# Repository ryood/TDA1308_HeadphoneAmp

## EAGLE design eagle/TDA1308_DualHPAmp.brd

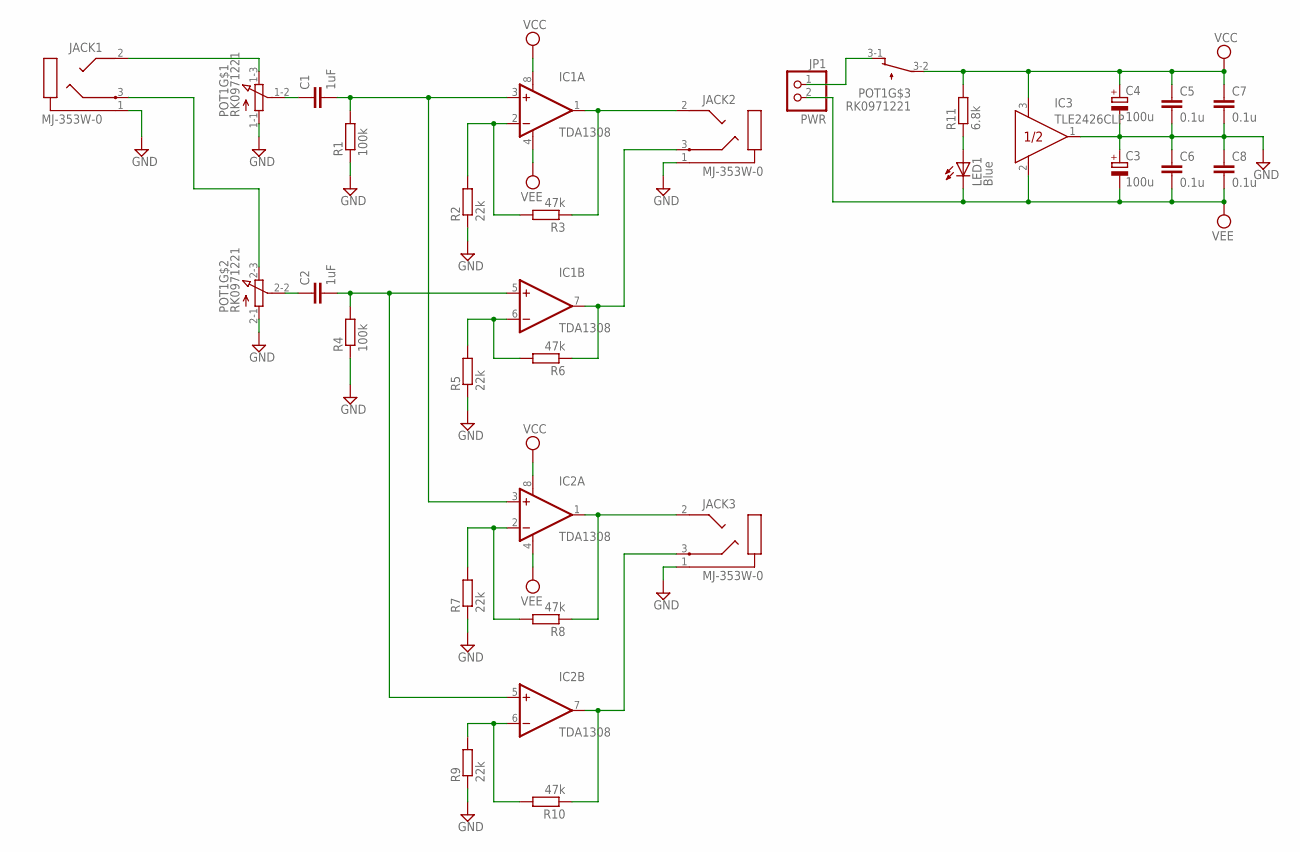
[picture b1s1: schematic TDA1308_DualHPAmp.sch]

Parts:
C1, C2: 1uF; C050-050X075
C3, C4: 100u; E2,5-7
C5, C7: 0.1u; C050-024X044
C6, C8: 0.1u; C025-024X044
IC1, IC2: TDA1308; DIL08
IC3: TLE2426CLP; TO226AA
JACK1, JACK2, JACK3: MJ-353W-0; MJ-3052W-0
JP1: PWR; 1X02
LED1: Blue; LED3MM
POT1: RK0971221
R1, R4: 100k; 0207/2V
R2, R7, R9: 22k; 0207/2V
R3, R6, R8, R10: 47k; 0207/2V
R5: 22k; 0207/7
R11: 6.8k; 0207/7

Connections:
GND: C3.+, C4.-, C5.2, C6.1, C7.2, C8.1, IC3.1 (OUT), JACK1.1, JACK2.1, JACK3.1, POT1.1-1 (A), POT1.2-1 (A), R1.1, R2.1, R4.1, R5.1, R7.1, R9.1
unnamed: JACK1.2, POT1.1-3 (E)
unnamed: JACK1.3, POT1.2-3 (E)
unnamed: C1.1, POT1.1-2 (S)
unnamed: C2.1, POT1.2-2 (S)
unnamed: C2.2, IC1.5 (+IN), IC2.5 (+IN), R4.2
unnamed: C1.2, IC1.3 (+IN), IC2.3 (+IN), R1.2
unnamed: IC1.2 (-IN), R2.2, R3.2
unnamed: IC1.1 (OUT), JACK2.2, R3.1
unnamed: IC1.6 (-IN), R5.2, R6.2
unnamed: JP1.1, POT1.3-1 (O)
unnamed: IC1.7 (OUT), JACK2.3, R6.1
unnamed: IC2.2 (-IN), R7.2, R8.2
unnamed: LED1.A, R11.1
unnamed: IC2.6 (-IN), R9.2, R10.2
unnamed: IC2.1 (OUT), JACK3.2, R8.1
unnamed: IC2.7 (OUT), JACK3.3, R10.1
VCC: C4.+, C5.1, C7.1, IC1.8 (V+), IC2.8 (V+), IC3.3 (IN), POT1.3-2, R11.2
VEE: C3.-, C6.2, C8.2, IC1.4 (V-), IC2.4 (V-), IC3.2 (COM), JP1.2, LED1.K (C)

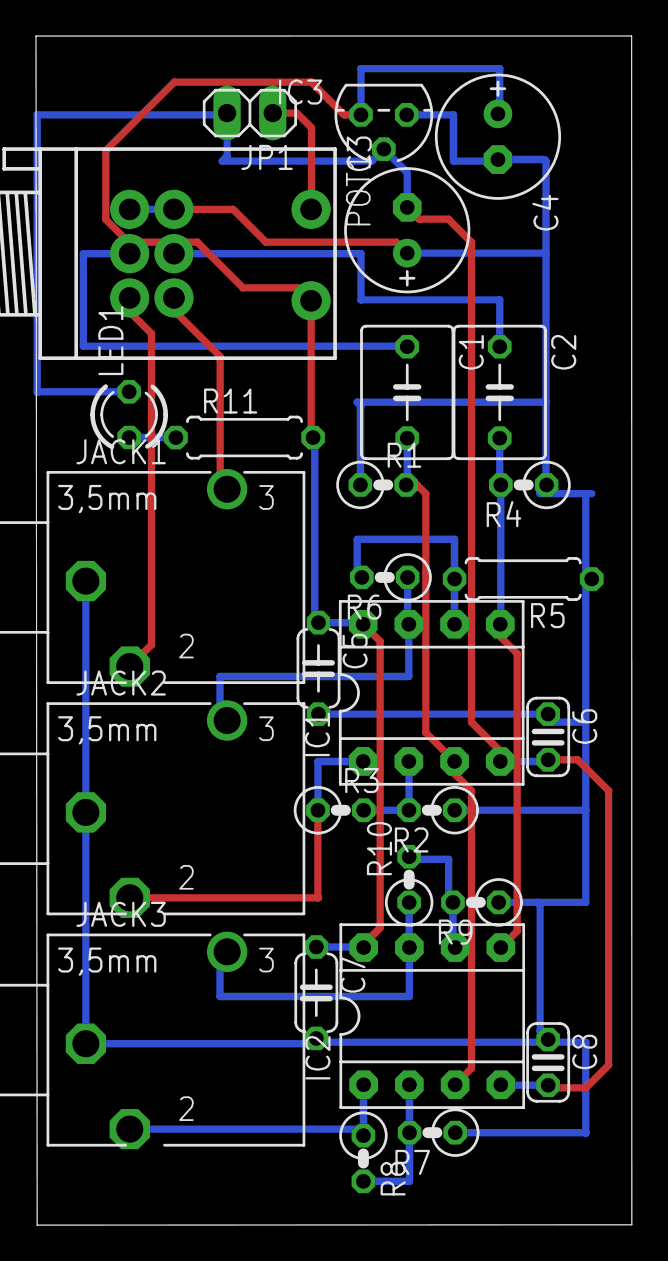
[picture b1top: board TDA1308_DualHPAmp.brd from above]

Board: 2 copper layers, 33.1 x 66.1 mm, 28 parts (0 on the bottom side), 19 nets.

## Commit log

2015-12-12 基板図修正（幅を削減）
2015-12-16 基板図にグリッドを追加
2016-01-06 基板図を修正
2016-01-08 update board design
2016-01-08 非反転増幅回路のRの位置を修正
2016-01-12 回路図、基板図(PNG)追加
2016-01-12 テスト表追加
2016-01-12 ケース加工図追加
